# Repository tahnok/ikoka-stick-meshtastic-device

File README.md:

# Ikoka Stick Meshtastic Device

# GOME Edition!!

https://ottawamesh.ca/

## Ikoka! (行こか!)

“行こか?” or “行こか!” is [Kansai dialect](https://en.wikipedia.org/wiki/Kansai_dialect) for “shall we go?” or “let’s go!”.

I hope that building these long-range Meshtastic designs inspires you to go on your next [DXing](https://en.wikipedia.org/wiki/DXing) adventure.

## Features

- LoRa
  - Up to 33 dBm (2 W) output power
  - 410–493 MHz (433 MHz band) or 850–930 MHz (868/915/923 MHz band)
- Bluetooth 5 LE
- Wi-Fi 4 (2.4 GHz)
- Lithium-ion battery with charging
- 0.96" OLED display

Feature set above depends on part selection.

### Hardware

### Parts Selection

Several options are available depending on the feature set you need.

#### Microcontroller

- [Seeed Studio XIAO-nRF52840](https://www.seeedstudio.com/Seeed-XIAO-BLE-nRF52840-p-5201.html) - Bluetooth 5/LE
- [Seeed Studio XIAO-ESP32-S3](https://www.seeedstudio.com/XIAO-ESP32S3-p-5627.html) - Bluetooth 5/LE and Wi-Fi 4 (2.4 GHz)

#### LoRa Module

This variant uses the E22P instead of the E22.
They are almost pin compatible except for 2 pins.

Pin 6 on the E22 is `RX_EN` and is connected to `SX126X_RXEN` in firmware.
On the E22P pin 6 is just `EN` and must be high in order to transmit or receive.

This pin is tied to 3.3V from the Xiaio, but can be reconnected to Xiao's pin 6 by cutting the jumper and putting a blob of solder.

Pin 7 is also technically different.
On the E22P it is `T/R CTRL`, which sets the module to transmit or receive. High means TX, low means RX.
This pin is connected to the radio's `DIO2` and it behaves correctly.

There's a washtastic variant that does this in software, see [commit](https://github.com/yellowcooln/MeshCore-washtastic-e22p/commit/3ebd5f18f94eb0c87fe2e88f7eaa14b53440a2b4)

#### Lithium-ion Battery (4.2V charging termination, optional)

- 21700 Lithium-ion battery cell (4.2V charge termination; holder: [BeilaMoo PA21700*1-SMT](https://www.beilamoo.com/sdm/1074412/4/pd-5180803/21061576-2986071/ONE_21700_Battery_Holder_with_Surface_Mount_SMT.html)/[MYOUNG BH-21700-B1BJ001](https://jlcpcb.com/partdetail/Myoung-BH_21700B1BJ001/C20606791))
- Lithium-polymer pouch battery cell (4.2V charge termination; connector: Molex PicoBlade 1x02P, pitch 1.25mm)
- Do not use both a 21700 and LiPo battery simultaneously, they will be shorted together in parallel

##### Wiring for Battery Charging

You will need a PicoBlade Female-to-Pigtail cable assembly such as Molex [218112-0200](https://www.molex.com/en-us/products/part-detail/2181120200). A compatible cable ships with Heltec Wireless and LILYGO LoRa products so you probably have spares you can use. [Muzi Works](https://muzi.works/products/battery-cable-molex-picoblade) and [Rokland](https://store.rokland.com/products/battery-connector-cables-battery-wires-jst-1-25-5pcs-for-lilygo-and-heltec) also sell compatible cables.

1. Trim the pigtail length to around 5cm if it is longer
2. Strip 2mm of insulation from each pigtail, then twist and tin the wire strands
3. Solder the red pigtail (or pin 1) to the BAT+ pad on the back of the XIAO module
4. Solder the black pigtail (or pin 2) to the BAT- pad on the back of the XIAO module
5. Plug the cable into the XIAO Charger connector on the Ikoka Stick

In my previous design, the [Ikoka Nano](https://github.com/ndoo/ikoka-nano-meshtastic-device), the XIAO module was SMD soldered onto the board, while the BAT+ pad was soldered through a plated through-hole via. However, the actual solder joint is buried and couldn't be inspected for continuity, quality and ensuring the BAT+ pad was not shorted to the BAT- pad.

In the interest of ease-of-assembly and keeping the XIAO module interchangeable, while not wasting the built-in battery charging circuit on XIAO modules, this approach was chosen instead.

#### OLED Display (Optional)

- Generic SSD1306 0.96" OLED display modules with 2.54mm pin headers [https://www.aliexpress.com/item/1005008077705181.html]((AliExpress))

**NOTE: check the order of the pins, this variant differs from the original**

 1. GND
 2. 3.3V
 3. SCL
 4. SDA

## Firmware

### GPIO Assignment

| XIAO Pin | Function | XIAO-nRF52840 | XIAO-ESP32-S3 |
|---|---|---|---|
| 1 (D0) | User button | 2 (P0.02) | 1 |
| 2 (D1) | EBYTE E22 - DIO1 | 3 (P0.03) | 2 |
| 3 (D2) | EBYTE E22 - RST | 28 (P0.28) | 3 |
| 4 (D3) | EBYTE E22 - BUSY | 29 (P0.29) | 4 |
| 5 (D4) | EBYTE E22 - SPI NSS | 4 (P0.04) | 5 |
| 6 (D5) | FREE | 5 (P0.05) | 6 |
| 7 (D6) | SSD1306 OLED - I2C SDA | 43 (P1.11) | 43 |
| 8 (D7) | SSD1306 OLED - I2C SCL | 44 (P1.12) | 44 |
| 9 (D8) | EBYTE E22 - SPI SCK | 45 (P1.13) | 7 |
| 10 (D9) | EBYTE E22 - SPI MISO | 46 (P1.14) | 8 |
| 11 (D10) | EBYTE E22 - SPI MOSI | 47 (P1.15) | 9 |
| 12 | SSD1306 OLED - 3.3V | 3V3 | 3V3 |
| 13 | GND | GND | GND |
| 14 | NC | 5V | 5V |

### Meshtastic Compatibility

The XIAO module is intended to be socketed with pin headers/pin sockets, to allow swapping out modules depending on what features are needed (Bluetooth, Wi-Fi, different power consumption profiles, etc.); Compatibility with official Meshtastic firmware depends on the inserted XIAO board.

#### XIAO-nRF52840

- EBYTE E22 LoRa
  - LoRa pins are identical to the officially-supported [Seeed Xiao NRF52840 Kit](https://www.seeedstudio.com/XIAO-nRF52840-Wio-SX1262-Kit-for-Meshtastic-p-6400.html) on [Meshtastic Web Flasher](https://flasher.meshtastic.org/)
  - LoRa will work out of the box on officially-supported firmware
  - Special consideration must be taken if using the E22-900M33S module
    - Set the transmit power to ≤ 9 dBm on first use (when setting the LoRa region)
    - **Transmit power must never be set greater than 9 dBm*- to avoid damaging the module's RF frontend
- SSD1306 OLED I2C
  - Pin D6/P1.11 and D7/P1.12 are [reserved for the L76K GPS module in the officially-supported variant](https://github.com/meshtastic/firmware/blob/152b8b1b0235bc461c6e4451fbcdac0987b8bf90/variants/seeed_xiao_nrf52840_kit/variant.h#L137-L138)
  - A custom firmware must be built to define these pins as I2C (TODO)
- User button
  - Pin D0/P0.02 is [reserved for the L76K GPS module in the officially supported variant](https://github.com/meshtastic/firmware/blob/152b8b1b0235bc461c6e4451fbcdac0987b8bf90/variants/seeed_xiao_nrf52840_kit/variant.h#L144)
  - A custom firmware must be built to define this pin as the user button (TODO)

### XIAO-ESP32-S3

- Pin definitions are different from the officially-supported [Seeed Xiao ESP32-S3 Kit](https://www.seeedstudio.com/Wio-SX1262-with-XIAO-ESP32S3-p-5982.html)
  - This is because Seeed uses GPIOs on the 30-pin board-to-board press-fit connector instead of the standard XIAO pins
  - A custom firmware must be built (TODO)

## PCB Renders

### PCB Top

### PCB Bottom

### Rotating GIF

(Rendered with [kicad-render](https://github.com/linalinn/kicad-render).)

# GOME Notes

If you want to generate this again, you need to install the [Microgramma](https://en.wikipedia.org/wiki/Microgramma_(typeface)) font, I got it [here](https://fontsgeek.com/fonts/Microgramma-D-Extended-Bold)

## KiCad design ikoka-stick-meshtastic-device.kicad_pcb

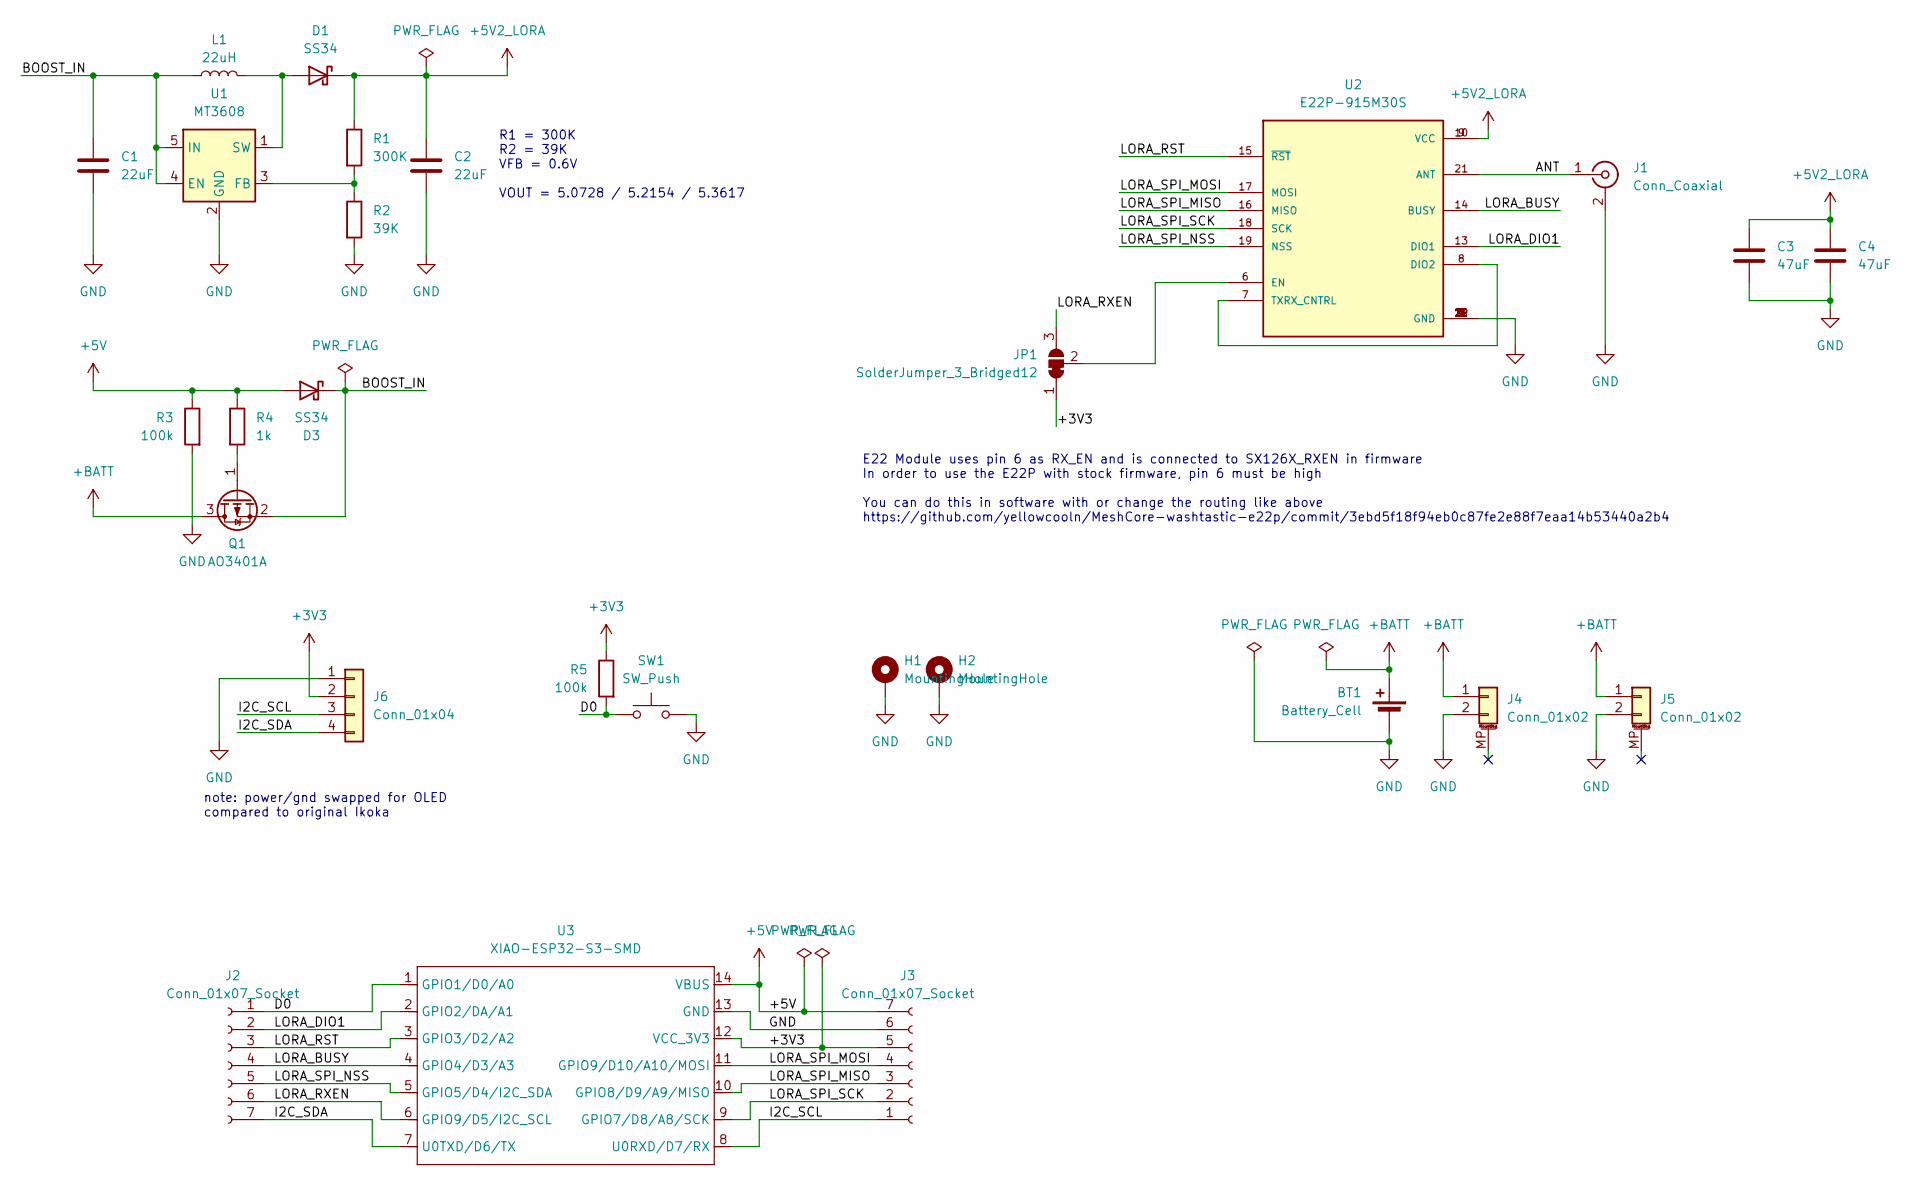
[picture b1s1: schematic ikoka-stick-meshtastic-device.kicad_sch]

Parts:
BT1: Battery_Cell; BatteryHolder_MYOUNG_BH-21700-B1BJ001_1x21700; LCSC C20606791
C1, C2: 22uF; C_0603_1608Metric; LCSC C59461
C3, C4: 47uF; C_0805_2012Metric; LCSC C16780
D1, D3: SS34; D_SMA; LCSC C8678
H1, H2: MountingHole; MountingHole_2.2mm_M2_Pad_Via
J1: Conn_Coaxial; SMA_Samtec_SMA-J-P-H-ST-EM1_EdgeMount; LCSC C5250058
J2, J3: Conn_01x07_Socket; PinSocket_1x07_P2.54mm_Vertical_SMD_Pin1Left; LCSC C42379199
J4, J5: Conn_01x02; Molex_PicoBlade_53261-0271_1x02-1MP_P1.25mm_Horizontal; LCSC C2905009
J6: Conn_01x04; PinSocket_1x04_P2.54mm_Vertical_SMD_Pin1Right; LCSC C46635840
JP1: SolderJumper_3_Bridged12; SolderJumper-3_P1.3mm_Bridged12_RoundedPad1.0x1.5mm_NumberL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
L1: 22uH; L_Sunlord_MWSA0624S; LCSC C408436
Q1: AO3401A; SOT-23; LCSC C15127
R1: 300K; R_0603_1608Metric; LCSC C23024
R2: 39K; R_0603_1608Metric; LCSC C23153
R3, R5: 100k; R_0603_1608Metric; LCSC C25803
R4: 1k; R_0603_1608Metric; LCSC C21190
SW1: SW_Push; SW_Push_1P1T_XKB_TS-1187A; LCSC C318884
U1: MT3608; SOT-23-6; LCSC C2932326
U2: E22P-915M30S; XCVR_E22-900M30S; PARTREV 1.2; LCSC C411294
U3: XIAO-ESP32-S3-SMD; XIAO-ESP32S3-DIP; LCSC C9900124959

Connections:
+3V3: J3.5, J6.2, JP1.1 (A), R5.1, U3.12 (VCC_3V3)
+5V: D3.2 (A), J3.7, R3.1, R4.1, U3.14 (VBUS)
+5V2_LORA: C2.1, C3.1, C4.1, D1.1 (K), R1.1, U2.9 (VCC), U2.10 (VCC)
+BATT: BT1.1 (+), J4.1, J5.1, Q1.3 (D)
/ANT: J1.1 (In), U2.21 (ANT)
/BOOST_IN: C1.1, D3.1 (K), L1.2, Q1.2 (S), U1.4 (EN), U1.5 (IN)
/D0: J2.1, R5.2, SW1.1, U3.1 (GPIO1/D0/A0)
/I2C_SCL: J3.1, J6.3, U3.8 (U0RXD/D7/RX)
/I2C_SDA: J2.7, J6.4, U3.7 (U0TXD/D6/TX)
/LORA_BUSY: J2.4, U2.14 (BUSY), U3.4 (GPIO4/D3/A3)
/LORA_DIO1: J2.2, U2.13 (DIO1), U3.2 (GPIO2/DA/A1)
/LORA_RST: J2.3, U2.15 (~RST), U3.3 (GPIO3/D2/A2)
/LORA_RXEN: J2.6, JP1.3 (B), U3.6 (GPIO9/D5/I2C_SCL)
/LORA_SPI_MISO: J3.3, U2.16 (MISO), U3.10 (GPIO8/D9/A9/MISO)
/LORA_SPI_MOSI: J3.4, U2.17 (MOSI), U3.11 (GPIO9/D10/A10/MOSI)
/LORA_SPI_NSS: J2.5, U2.19 (NSS), U3.5 (GPIO5/D4/I2C_SDA)
/LORA_SPI_SCK: J3.2, U2.18 (SCK), U3.9 (GPIO7/D8/A8/SCK)
GND: BT1.2 (-), C1.2, C2.2, C3.2, C4.2, H1.1, H2.1, J1.2 (Ext), J3.6, J4.2, J5.2, J6.1, R2.2, R3.2, SW1.2, U1.2 (GND), U2.1 (GND), U2.2 (GND), U2.3 (GND), U2.4 (GND), U2.5 (GND), U2.11 (GND), U2.12 (GND), U2.20 (GND), U2.22 (GND), U3.13 (GND)
unnamed: D1.2 (A), L1.1, U1.1 (SW)
unnamed: JP1.2 (C), U2.6 (EN)
unnamed: Q1.1 (G), R4.2
unnamed: R1.2, R2.1, U1.3 (FB)
unnamed: U2.7 (TXRX_CNTRL), U2.8 (DIO2)

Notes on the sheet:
note: power/gnd swapped for OLED compared to original Ikoka
R1 = 300K R2 = 39K VFB = 0.6V VOUT = 5.0728 / 5.2154 / 5.3617
E22 Module uses pin 6 as RX_EN and is connected to SX126X_RXEN in firmware In order to use the E22P with stock firmware, pin 6 must be high You can do this in software with or change the routing like above https://github.com/yellowcooln/MeshCore-washtastic-e22p/commit/3ebd5f18f94eb0c87fe2e88f7eaa14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

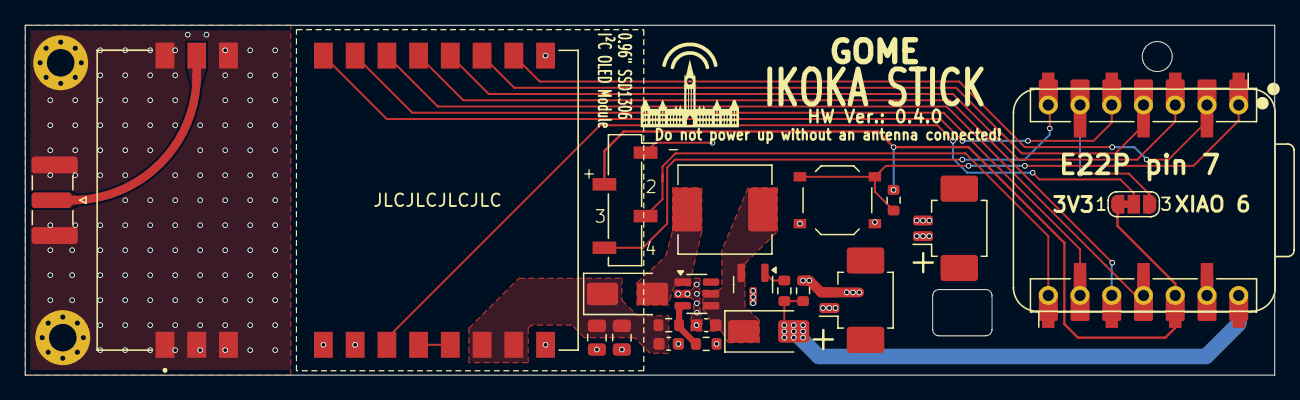
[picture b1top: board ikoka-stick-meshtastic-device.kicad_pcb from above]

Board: 2 copper layers, 100.0 x 28.0 mm, 27 parts (1 on the bottom side), 23 nets.

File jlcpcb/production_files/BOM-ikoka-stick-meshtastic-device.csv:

Comment,Designator,Footprint,LCSC,Quantity
100k,"R3,R5",R_0603_1608Metric,C25803,2
1k,R4,R_0603_1608Metric,C21190,1
22uF,"C1,C2",C_0603_1608Metric,C59461,2
22uH,L1,L_Sunlord_MWSA0624S,C408436,1
300K,R1,R_0603_1608Metric,C23024,1
39K,R2,R_0603_1608Metric,C23153,1
47uF,"C3,C4",C_0805_2012Metric,C16780,2
AO3401A,Q1,SOT-23,C15127,1
Battery_Cell,BT1,BatteryHolder_MYOUNG_BH-21700-B1BJ001_1x21700,C20606791,1
Conn_01x02,"J4,J5",Molex_PicoBlade_53261-0271_1x02-1MP_P1.25mm_Horizontal,C2905009,2
Conn_01x04,J6,PinSocket_1x04_P2.54mm_Vertical_SMD_Pin1Right,C42379197,1
Conn_01x07_Socket,"J2,J3",PinSocket_1x07_P2.54mm_Vertical_SMD_Pin1Left,C42379199,2
Conn_Coaxial,J1,SMA_Samtec_SMA-J-P-H-ST-EM1_EdgeMount,C5250058,1
E22P-915M30S,U2,XCVR_E22-900M30S,C51912672,1
MT3608,U1,SOT-23-6,C2932326,1
SS34,"D1,D3",D_SMA,C8678,2
SW_Push,SW1,SW_Push_1P1T_XKB_TS-1187A,C318884,1

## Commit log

2026-01-16 Baseline fixes to font, OLED header part change, exclude U3 and rotate J2,J3 properly
2026-03-13 use E22P, swap I2C power/gnd
2026-04-01 final? rev 0.4.0
2026-04-05 pdf schematic export
